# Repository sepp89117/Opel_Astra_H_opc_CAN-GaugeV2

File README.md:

# Opel_Astra_H_opc_CAN-GaugeV2
New version, looks like BC from Nissan GT-R and uses large touchscreen
Needs Waveshare 4inch RPi LCD (C) ILI9486 display and lib

<br>
Watch demo on https://youtu.be/G2oHpHkk6c8
<br>
You may need to comment out ``#include "utils/debug.h"`` in TeensyThreads.h (line 29)
<br>
<h2>Hardware:</h2><br>
 - Teensy 4.0<br>
 - 2x Waveshare CAN Board SN65HVD230<br>
 - Waveshare 4inch RPi LCD (C) ILI9486 with XPT2046 Touch<br>
 - LM2596 DC/DC Converter - set 5.0 Volt output<br>
<br>
<h2>Car:</h2> Opel Astra H opc 2007<br>
<br>
<h2>Interface 1 connection:</h2> HSCAN 500 kBaud (Pin 6 and 14 on OBD connector)<br>
<h2>Interface 2 connection:</h2> MSCAN 33.3 kBaud (Pin 1 and 5(GND) on OBD connector)<br>
<br>
<h2>Circuit board layout (EAGLE)</h2><br>
<br>
<br>
In order to be able to control the brightness of the LCD, you have to bridge these contacts on the back of the LCD.<br>
<br>
Then a wire must be laid from Teensy pin 3 to LCD pin 12 (included in Circuit-Board-Rev-1.1).<br>

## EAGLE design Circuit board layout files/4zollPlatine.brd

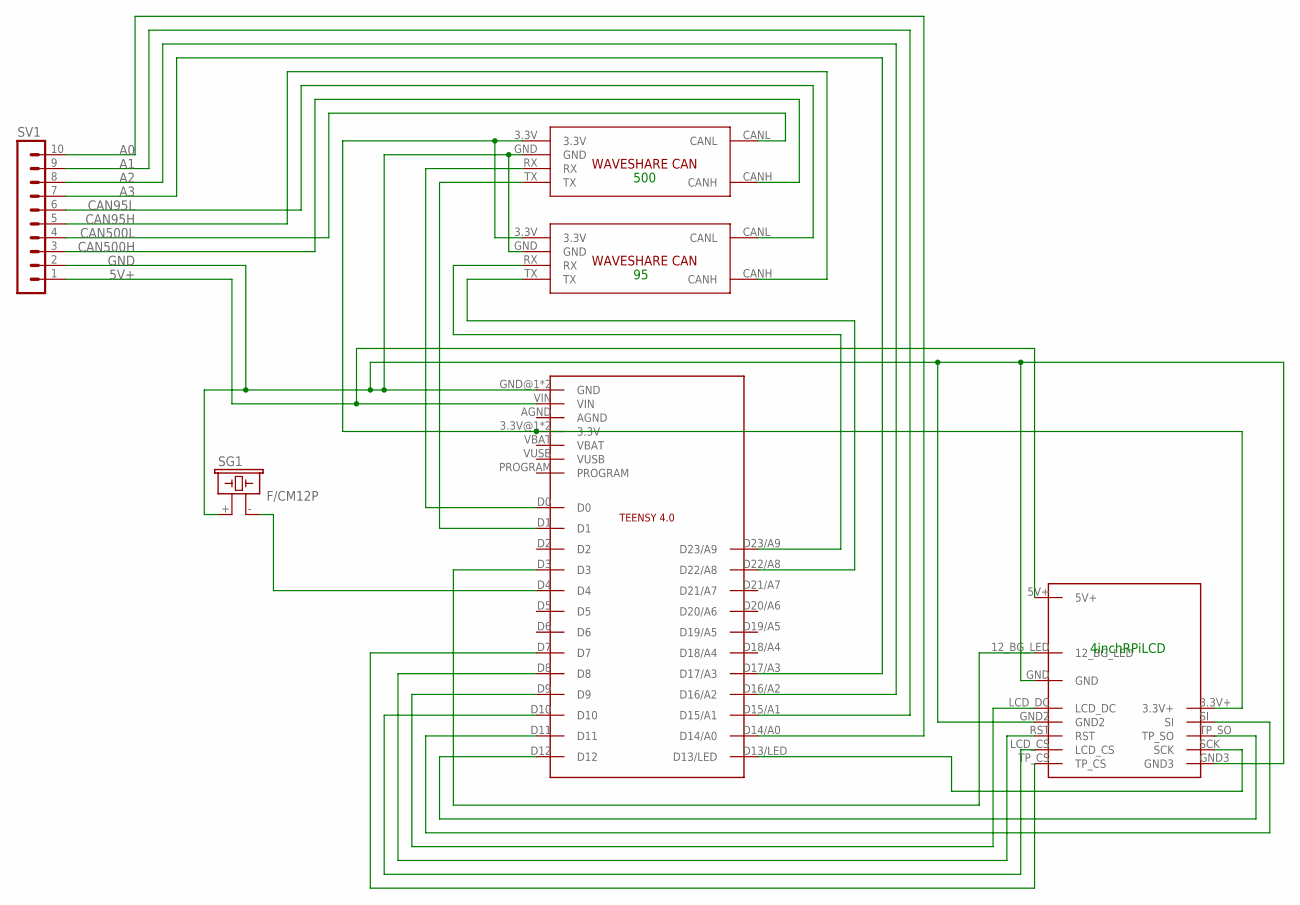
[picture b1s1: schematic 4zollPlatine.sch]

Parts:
95, 500: CAN_MODULE; CAN_BOARD
SG1: F/CM12P
SV1: MA10-1
U$1: TEENSY4.0
U$2: 4INCH_RPI_LCD_DEV; 4INCH_RPI_LCD_FP

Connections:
5V+: SV1.1, U$1.VIN, U$2.5V+
A0: SV1.10, U$1.D14/A0
A1: SV1.9, U$1.D15/A1
A2: SV1.8, U$1.D16/A2
A3: SV1.7, U$1.D17/A3
CAN95H: 95.CANH, SV1.5
CAN95L: 95.CANL, SV1.6
CAN500H: 500.CANH, SV1.3
CAN500L: 500.CANL, SV1.4
GND: 95.GND, 500.GND, SG1.+ (1), SV1.2, U$1.GND@1 (GND), U$1.GND@2 (GND), U$2.GND, U$2.GND2, U$2.GND3
unnamed: 95.3.3V, 500.3.3V, U$1.3.3V@1 (3.3V), U$1.3.3V@2 (3.3V), U$2.3.3V+
unnamed: U$1.D3, U$2.12_BG_LED
unnamed: SG1.- (2), U$1.D4
unnamed: U$1.D11, U$2.SI
unnamed: 500.RX, U$1.D0
unnamed: 500.TX, U$1.D1
unnamed: 95.RX, U$1.D23/A9
unnamed: 95.TX, U$1.D22/A8
unnamed: U$1.D7, U$2.TP_CS
unnamed: U$1.D10, U$2.LCD_CS
unnamed: U$1.D8, U$2.RST
unnamed: U$1.D9, U$2.LCD_DC
unnamed: U$1.D13/LED, U$2.SCK
unnamed: U$1.D12, U$2.TP_SO

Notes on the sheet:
500
4inchRPiLCD

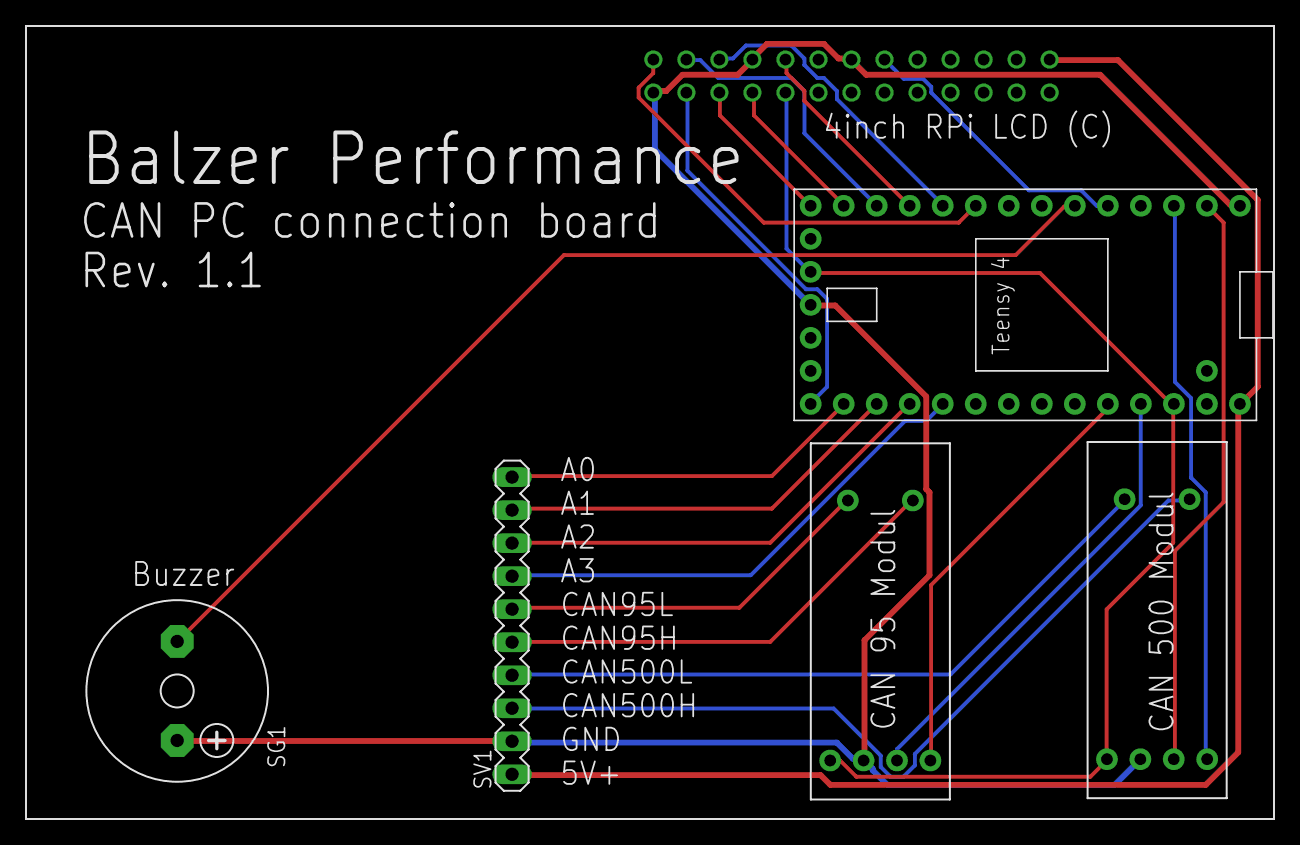
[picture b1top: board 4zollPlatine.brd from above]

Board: 2 copper layers, 96.0 x 61.0 mm, 6 parts (0 on the bottom side), 24 nets.

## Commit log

2021-01-31 Update
    Add all special libs and add brightness control to bc
2021-01-31 Update opc3BC_XL.ino
    Correction value for atmospheric pressure added
2021-02-12 Add files via upload
    EAGLE files for connection board
2021-03-27 Update opc3BC_XL.ino
    Added knock retard values and corrected ignition spark angle value calculation
2021-04-03 Updated fault code and lambda value
    Updated fault code decoding and lambda value
2021-04-03 Newest Version of CAN-Analysis
2021-04-04 Added settings menu
    Added settings menu
2021-05-02 Adapter for mounting in original display housing
2022-07-30 Update opc3BC_XL.ino
    Gear indicator added and fix for display type a/c
2022-07-30 Update ILI9486_t3n.h
    Fix for display type a/c
2024-06-24 Add files via upload
    The tools, which I used together with an Arduino Uno and a CAN-BUS Shield V1.2 for reverse engineering.
    https://wiki.seeedstudio.com/CAN-BUS_Shield_V1.2/
2024-06-29 Add files via upload
    Optional code for usage with UART CAN modules
